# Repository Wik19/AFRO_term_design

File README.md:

Automatic Fault Recognition for Ornithopters

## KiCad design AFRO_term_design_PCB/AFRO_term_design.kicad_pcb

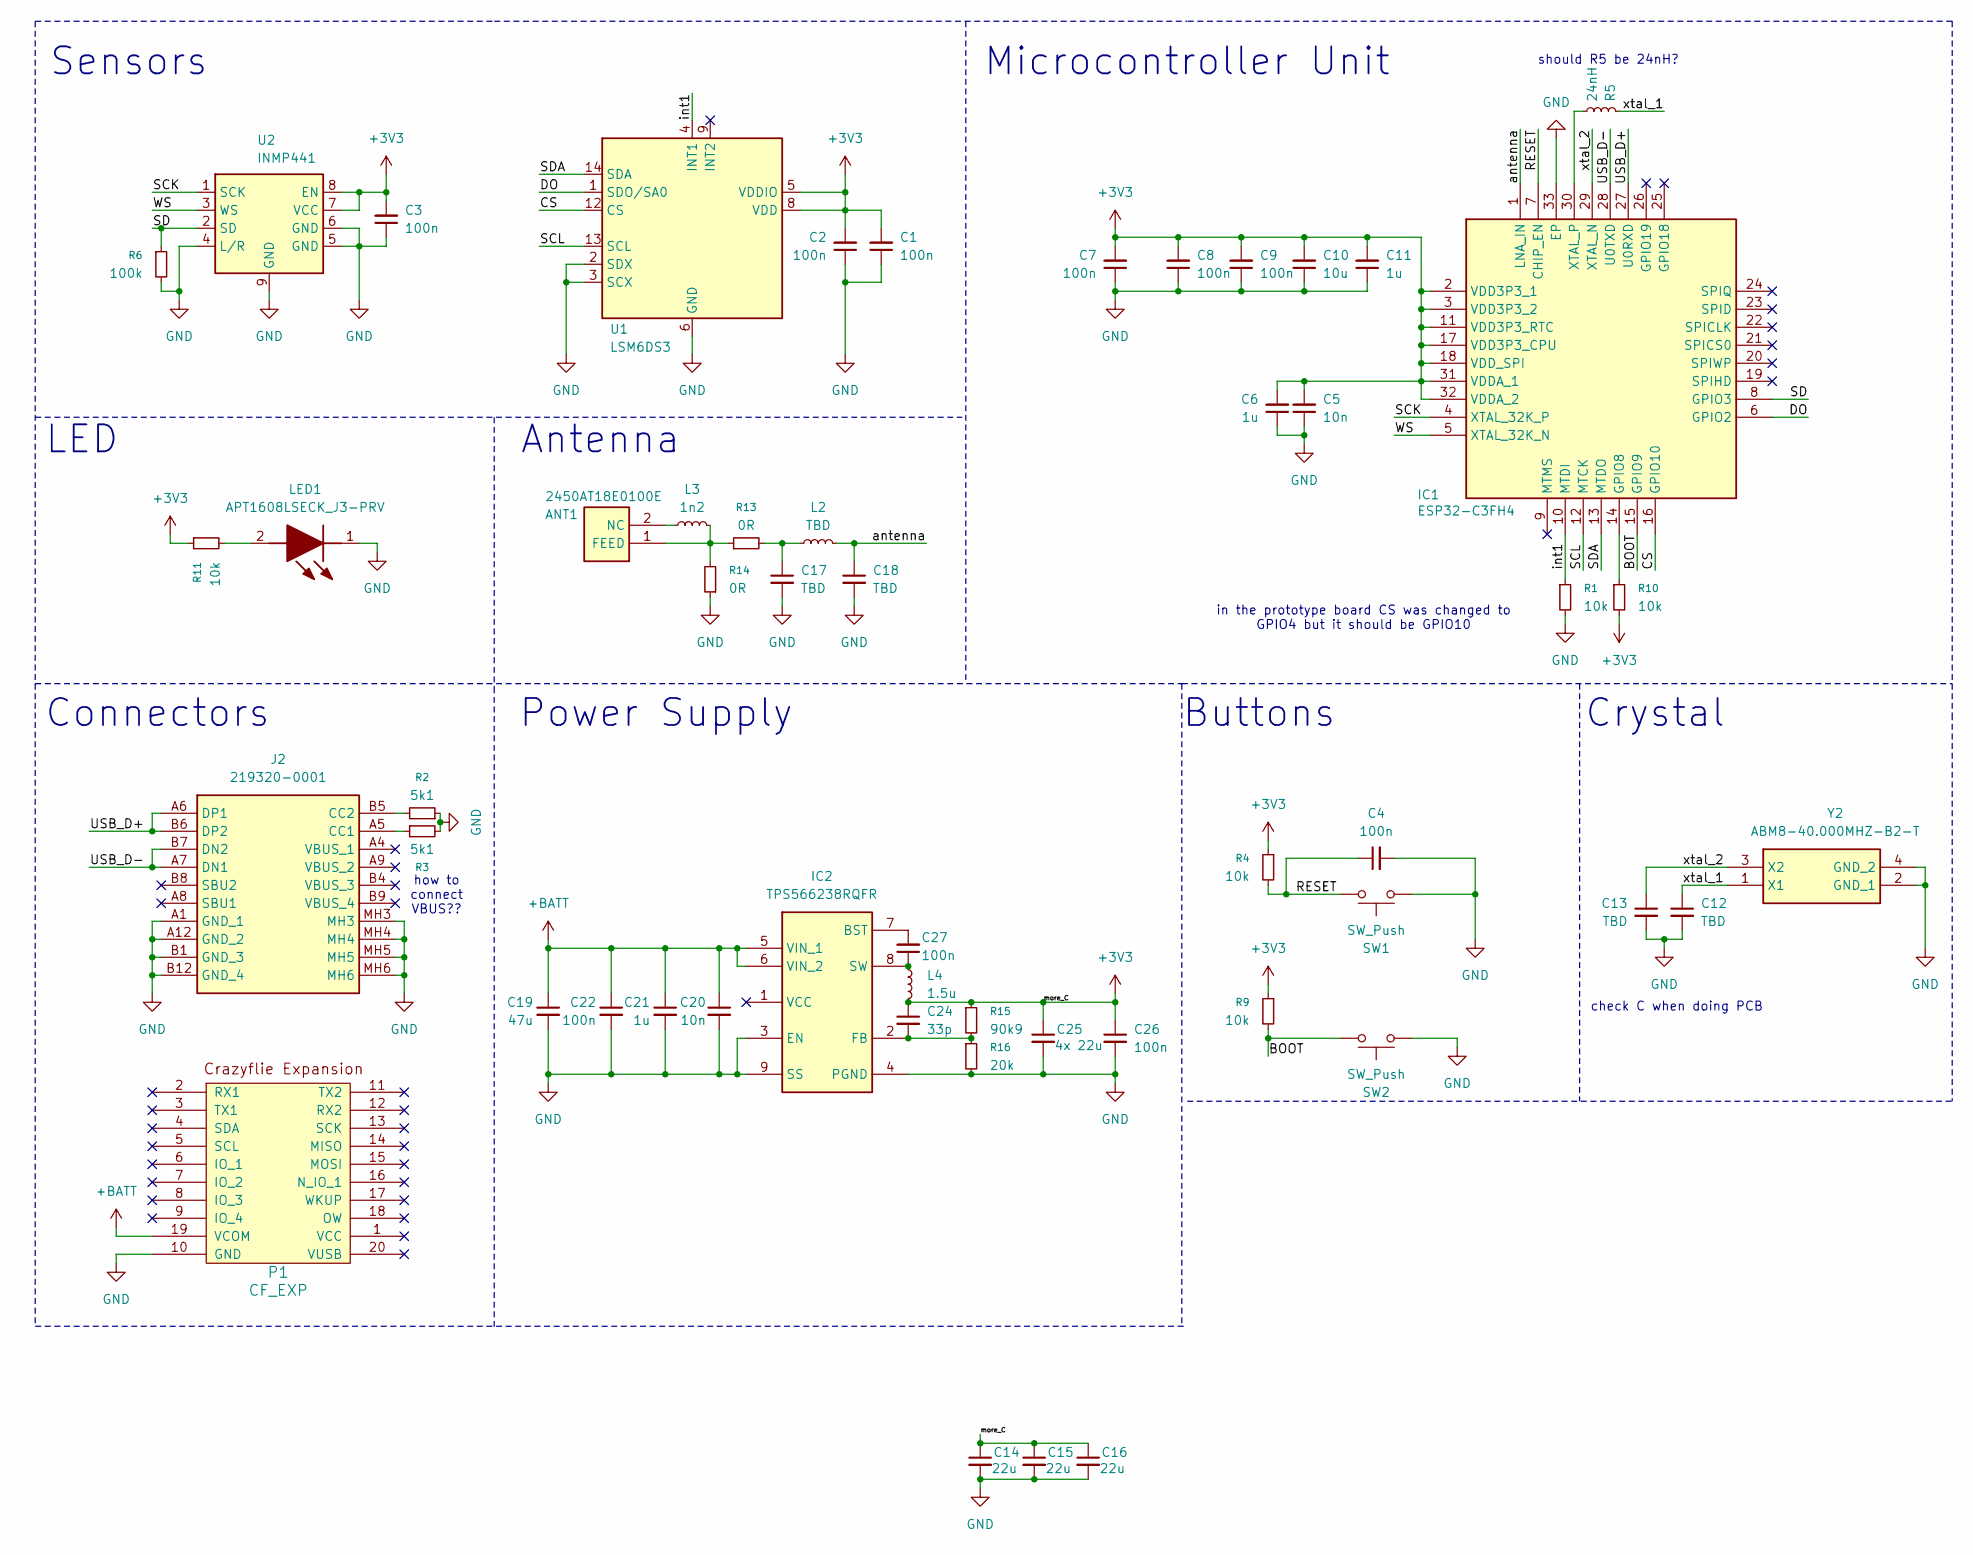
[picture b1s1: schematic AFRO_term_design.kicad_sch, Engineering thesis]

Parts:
ANT1: 2450AT18E0100E; ANTC3216X130N; Mouser Part Number 609-2450AT18E0100E
C1, C2, C3, C4, C7, C8, C9, C22, C26, C27: 100n; C_0603_1608Metric
C5, C20: 10n; C_0603_1608Metric
C6, C11, C21: 1u; C_0603_1608Metric
C10: 10u; C_0603_1608Metric
C12, C13, C17, C18: TBD; C_0603_1608Metric
C14, C15, C16: 22u; C_0603_1608Metric
C19: 47u; CAPC3216X229N
C24: 33p; C_0603_1608Metric
C25: 4x 22u; C_0603_1608Metric
IC1: ESP32-C3FH4; QFN50P500X500X90-33N-D; Mouser Part Number 356-ESP32-C3FH4
IC2: TPS566238RQFR; Mouser Part Number 595-TPS566238RQFR
J2: 219320-0001; 2193200001; Mouser Part Number 538-219320-0001
L2: TBD; L_0402_1005Metric
L3: 1n2; INDC1608X95N
L4: 1.5u; 74438357015
LED1: APT1608LSECK_J3-PRV; APT1608CGCK; Mouser Part Number 604-APT1608LSECKJ3RV
P1: CF_EXP; drone_connector
R1, R4, R9, R10, R11: 10k; R_0603_1608Metric
R2, R3: 5k1; R_0603_1608Metric
R5: 24nH; MHQ1005
R6: 100k; R_0603_1608Metric
R13, R14: 0R; R_0603_1608Metric
R15: 90k9; R_0603_1608Metric
R16: 20k; R_0603_1608Metric
SW1, SW2: SW_Push; 435151014824
U1: LSM6DS3; LGA-14_3x2.5mm_P0.5mm_LayoutBorder3x4y
U2: INMP441
Y2: ABM8-40.000MHZ-B2-T; ABM810000MHZ12D2W; Mouser Part Number 815-ABM8-40-B2-T

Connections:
+3V3: C1.2, C2.2, C3.2, C5.2, C6.2, C7.2, C8.2, C9.2, C10.2, C11.2, C14.1, C15.1, C16.1, C24.1, C25.1, C26.1, IC1.2 (VDD3P3_1), IC1.3 (VDD3P3_2), IC1.11 (VDD3P3_RTC), IC1.17 (VDD3P3_CPU), IC1.18 (VDD_SPI), IC1.31 (VDDA_1), IC1.32 (VDDA_2), L4.2, R4.1, R9.1, R10.2, R11.1, R15.1, U1.5 (VDDIO), U1.8 (VDD), U2.7 (VCC), U2.8 (EN)
+BATT: C19.1, C20.1, C21.1, C22.1, IC2.5 (VIN_1), IC2.6 (VIN_2), P1.19 (VCOM)
/BOOT: IC1.15 (GPIO9), R9.2, SW2.1
/CS: IC1.16 (GPIO10), U1.12 (CS)
/DO: IC1.6 (GPIO2), U1.1 (SDO/SA0)
/RESET: C4.1, IC1.7 (CHIP_EN), R4.2, SW1.1
/SCK: IC1.4 (XTAL_32K_P), U2.1 (SCK)
/SCL: IC1.12 (MTCK), U1.13 (SCL)
/SD: IC1.8 (GPIO3), R6.1, U2.2 (SD)
/SDA: IC1.13 (MTDO), U1.14 (SDA)
/USB_D+: IC1.27 (U0RXD), J2.A6 (DP1), J2.B6 (DP2)
/USB_D-: IC1.28 (U0TXD), J2.A7 (DN1), J2.B7 (DN2)
/WS: IC1.5 (XTAL_32K_N), U2.3 (WS)
/antenna: C18.1, IC1.1 (LNA_IN), L2.2
/int1: IC1.10 (MTDI), R1.1, U1.4 (INT1)
/xtal_1: C12.1, R5.1, Y2.1 (X1)
/xtal_2: C13.1, IC1.29 (XTAL_N), Y2.3 (X2)
unnamed: ANT1.1 (FEED), L3.2, R13.1, R14.2
unnamed: ANT1.2 (NC), L3.1
unnamed: C17.1, L2.1, R13.2
unnamed: IC1.14 (GPIO8), R10.1
unnamed: IC1.30 (XTAL_P), R5.2
unnamed: C27.2, IC2.7 (BST)
unnamed: C24.2, IC2.2 (FB), R15.2, R16.1
unnamed: C27.1, IC2.8 (SW), L4.1
unnamed: J2.A5 (CC1), R3.1
unnamed: J2.B5 (CC2), R2.2
unnamed: LED1.2 (A), R11.2

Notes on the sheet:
Power Supply
should R5 be 24nH?
check C when doing PCB
Antenna
Microcontroller Unit
in the prototype board CS was changed to GPIO4 but it should be GPIO10
how to connect VBUS??
Sensors
Connectors
Crystal
LED
Buttons

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
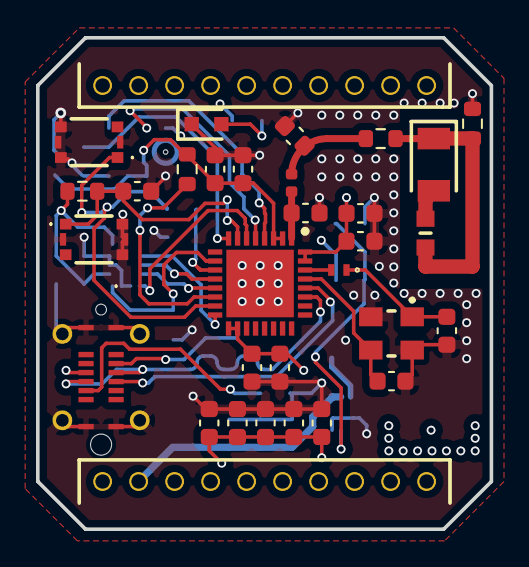
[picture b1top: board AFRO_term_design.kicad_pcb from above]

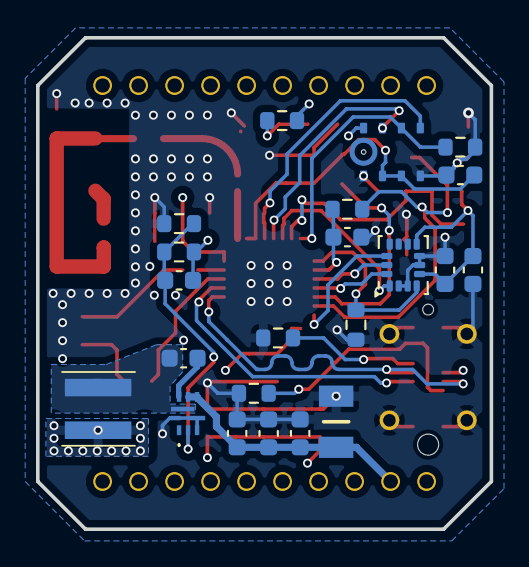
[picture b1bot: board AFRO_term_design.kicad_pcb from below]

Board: 4 copper layers, 25.2 x 27.3 mm, 53 parts (22 on the bottom side), 29 nets.

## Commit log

2025-05-07 main.py, working. Plotting everything via UART - imu at 104Hz
2025-05-07 Add data collection script for IMU and microphone using ESP32
2025-05-07 TCP Works! Enhance data collection and processing for IMU and audio
    - Refactor data collection from serial to socket communication for ESP32.
    - Implement structured packet handling for IMU and audio data.
    - Update audio sample processing to handle 24-bit data correctly.
    - Improve error handling and logging during data reception.
    - Add functionality to plot collected IMU and audio data.
2025-05-14 now we can listen to audio but it still does not work and there is a lot of lose
2025-05-14 Enhance data processing script: reduce listen duration, improve data reception handling, add CSV and WAV export functionality for IMU and audio data, and implement better error handling and logging.
2025-06-20 Everything works, Microphone tasks are scheduled with dual buffer method, IMU collects the data in 3 second frames
2025-06-20 added KiCAD files, must update schematic
2025-06-20 fixed the sensors pins to match the datasheet
2025-06-20 added all main components (w/o PSU)
2025-06-20 Quartz crystal connected
2025-06-23 reorganized the whole PCB schematic + added back-boost, might remove later
2025-06-23 reorganized the whole PCB schematic + added back-boost, might remove later...
2025-06-25 temp
2025-06-25 organized the schematic - without the suggested changes
2025-06-25 changed programming pins, fixed antenna, fixed programming logic with pull-up resistor on GPIO9. I chyba tyle, nie?
2025-06-25 changed interrupt pin from GPIO8 to GPIO5
2025-06-26 added LED to PSU, deciding how to add LEDs to mcu
2025-07-04 added almost all the footprints (added mic fp), must update power supply
2025-07-04 new buck converter
2025-07-07 added all footprints except LEDs
2025-07-07 started working on the PCB layout
2025-07-28 Initial PCB components placement
2025-08-25 aaaa
2025-08-25 connected part of the IMU and added LED, need to connect mic and antenna. Also check connections 3V3 to MCU
2025-09-06 made more connections - must redo the usb to mcu connection
2025-09-08 change the pcb layout
2025-09-11 modify antenna connection and finish placing the capacitors & voltage stabilizer / coil
2025-09-19 added antenna path, might change position later
2025-09-23 almost finished. Maybe rotate antenna 90deg. Correct errors.
2025-09-29 finished all connections and moved the antenna, still need to run DRC
2025-09-30 finished, hopefully
2025-10-01 unconnected traces fixed, under 0.15mm clearance violation solved
2025-10-02 removed the texts and replaced L3 with a 1.6x0.8mm one
